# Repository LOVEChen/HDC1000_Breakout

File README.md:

HDC1000 Breakout Board
======================

Here are Eagle files for my HDC1000 Breakout Board. It should work with the HDC1008 too, but I haven't tested it.

<p align="center">
  
</p>

The HDC1000 is a digital humidity sensor with integrated temperature sensor. 

More info and datasheet: http://www.ti.com/product/HDC1000.

Arduino library: https://github.com/ftruzzi/HDC1000-Arduino.

Blog post: http://b.truzzi.me/hdc1000-temperature-and-humidity-sensor-breakout-with-arduino-library/

##Features and parts list:

* **U1:** HDC1000 IC from Texas Instruments, DSBGA-8 package.
* **C1:** 0.1uF 0805 package decoupling cap.
* **R1,R2:** 4.7k-10k ohm, 0805 package. I2C pull-up resistors.
* **R3:** 10k ohm, 0805 package. Pull-up resistor to VCC, for the DRDYN pin. Leave the pin floating if not used.
* **R4, R5:** 10k ohm, pull-down resistors to GND for address selection.
* **ADR0, ADR1** solder jumpers to VCC, connect to change the chip address (default: 0x41).

You can visit my website at www.truzzi.me.

Any suggestions or comments are appreciated!

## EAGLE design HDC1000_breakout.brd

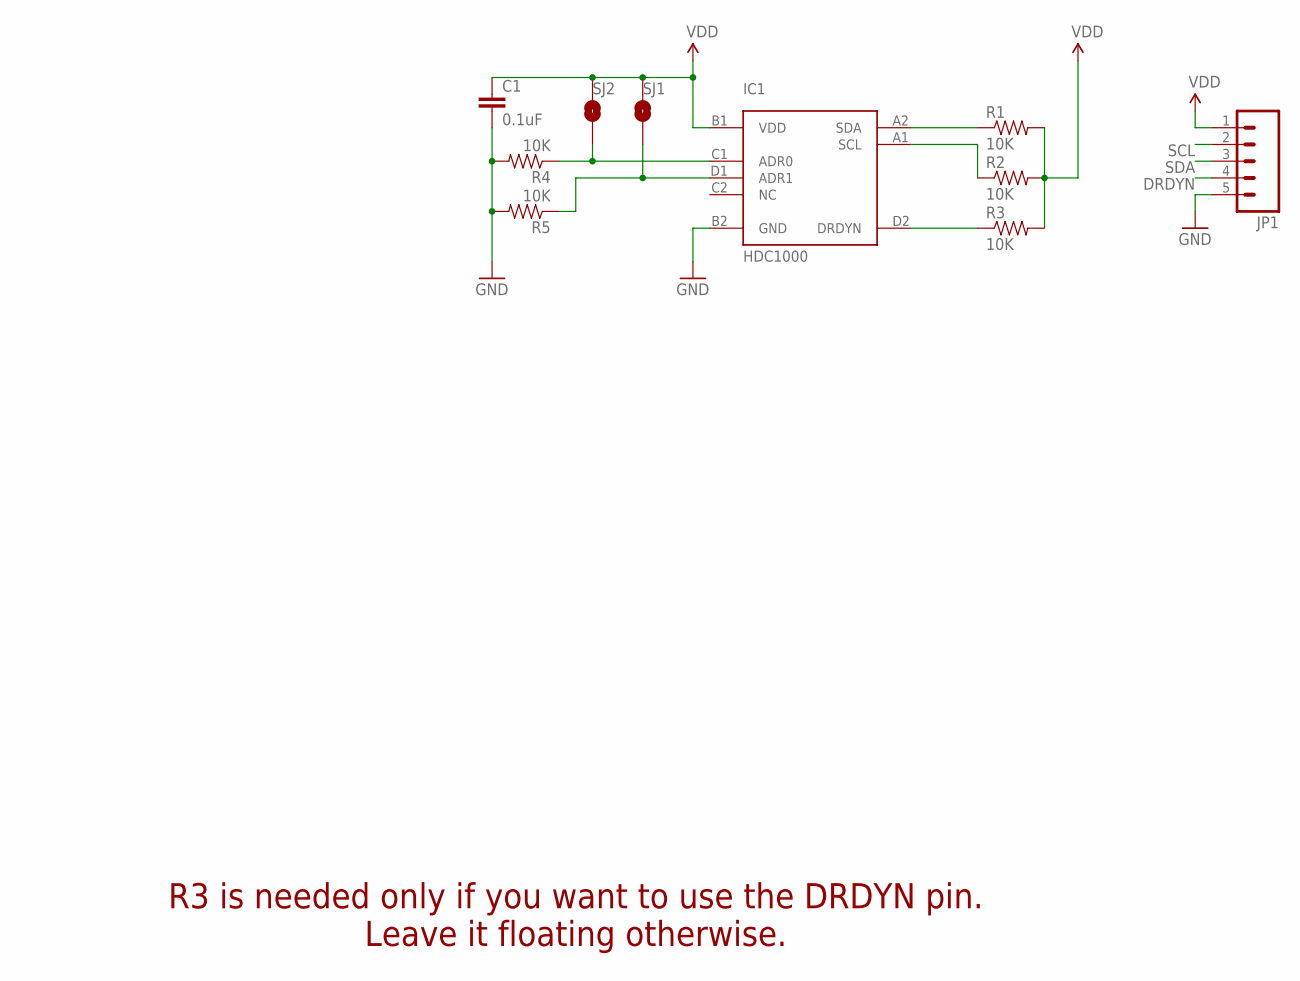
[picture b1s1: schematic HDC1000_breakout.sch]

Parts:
C1: 0.1uF; 0805
IC1: HDC1000; DSBGA_8_YPA
JP1: M05LOCK; 1X05_LOCK
R1, R2, R3, R4, R5: 10K; 0805
SJ1, SJ2: SOLDERJUMPERNO; SJ_2S-NO

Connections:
DRDYN: IC1.D2 (DRDYN), JP1.4, R3.1
GND: C1.2, IC1.B2 (GND), JP1.5, R4.2, R5.2
unnamed: IC1.D1 (ADR1), R5.1, SJ1.2
unnamed: IC1.C1 (ADR0), R4.1, SJ2.2
SCL: IC1.A1 (SCL), JP1.2, R2.1
SDA: IC1.A2 (SDA), JP1.3, R1.1
VDD: C1.1, IC1.B1 (VDD), JP1.1, R1.2, R2.2, R3.2, SJ1.1, SJ2.1

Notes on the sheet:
R3 is needed only if you want to use the DRDYN pin. Leave it floating otherwise.

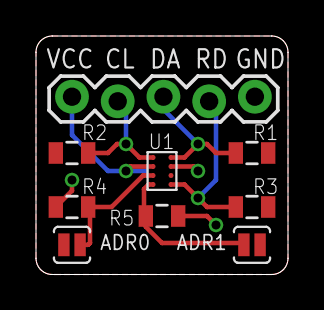
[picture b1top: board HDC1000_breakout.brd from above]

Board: 2 copper layers, 14.0 x 13.2 mm, 10 parts (1 on the bottom side), 7 nets.

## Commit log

2015-01-30 :lollipop: Added .gitattributes & .gitignore files
2015-01-30 First release.
2015-01-30 Added image.
2015-01-30 Fixed VCC plane.
2015-01-30 Updated image

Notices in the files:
HDC1000_breakout.sch:
LICENSE: Released under CC BY-NC-SA 4.0
parts and their libraries:
SparkFun-Passives: Licensing: Creative Commons ShareAlike 4.0 International - https://creativecommons.org/licenses/by-sa/4.0
